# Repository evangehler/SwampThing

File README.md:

# **SwampThing**
Beginning of a standalone Juno-106 inspired DCO monosynth for UF AES. Built around Raspberry Pi Pico Microcontroller.

## **Project Status**
| Component         | Designed  | Prototyped  | PCB / Finalized |
| -----             | --------  | ----------- | --------------- |
| DCO Saw-core      | X         | X           |                 |
| DCO Pulse / PWM   | X         | X           |                 |
| DCO SUB           | X         |             |                 |
| Blend             | X         |             |                 |
| MIDI USB          | X         | X           |                 |
| MIDI DIN          | X         | X           |                 |
| VCF               | X         | X           |                 |
| EG                | X         | X           |                 |
| VCA               | X         | X           |                 |
| Power Solution    |           |             |                 |
| Output            |           |             |                 |

# Table of Contents
- [Installation / Build](#installation--build)
  - [Prereqs](#prereqs)
  - [Build Steps](#build-steps)
  - [Quick Build & Flash](#quick-build--flash)
  - [Manual Flashing](#manual-flashing)
  - [I/O Notes](#io-notes)
- [Architecture](#architecture)
  - [Component Diagram](#component-diagram)
  - [MIDI](#midi)
    - [USB MIDI](#usb-midi-implemented)
    - [DIN MIDI](#din-midi-planned)
  - [Digitally Controlled Oscillator (DCO)](#digitally-controlled-oscillator-dco)
    - [SAW](#saw)
    - [PULSE / PWM](#pulse--pwm)
    - [SUB OSC](#sub-osc)
    - [BLEND](#blend)
  - [Envelope Generator (EG)](#envelope-generator-eg)
  - [Voltage Controlled Amplifier (VCA)](#voltage-conrolled-amplifier-vca)
  - [Voltage Controlled Filter (VCF)](#voltage-controlled-filter-vcf)
  - [Power Solution](#power-solution)
- [Incomplete BOM](#incomplete-bom)

# Installation / Build
MIDI control, oscillator reset signals, charge voltage and envelope gates are derived from a Raspberry Pi Pico.

### Prereqs
- [VS Code](https://code.visualstudio.com/)
- [Raspberry Pi Pico VS Code Extension](https://marketplace.visualstudio.com/items?itemName=raspberry-pi.raspberry-pi-pico)

### Build Steps
1. Clone this repo
2. Open the `src` folder in VS Code (not the root folder!)
3. Open a PowerShell terminal in VS Code
4. Run:
```powershell
mkdir build
cd build
cmake -G "Ninja" ..
cmake --build .
```
5. The `.uf2` file will be in `build/SwampThing.uf2`

### Quick Build & Flash
- Press `Ctrl+Shift+B` to build and flash in one step - nifty!

### Manual Flashing
1. Hold BOOTSEL on your Pico and plug it in
2. Drag `SwampThing.uf2` onto the Pico drive

### I/O Notes:

| Function            | GPIO #     | 
| -----               | --------   | 
| Clock output        | 13         |
| CV output           | 14         |
| Gate output         | 12         |

# Architecture
## Component Diagram:

## MIDI:

### USB MIDI (Implemented)
SwampThing appears as a **class-compliant USB MIDI device** over the Pico’s micro-USB port using TinyUSB.

### DIN MIDI (Planned)

5-pin DIN MIDI IN (with opto-isolation and UART at 31.25 kbps) is planned. DIN and USB MIDI will eventually share the same internal note/gate handling.

## Digitally Controlled Oscillator (DCO):

### SAW
Juno-style ramp core. A TL074 op-amp integrator generates a rising ramp, NPN transistor reset discharges the timing capacitor at a rate set by the microcontroller clock. Pitch is set by the reset clock (GPIO 13). Ramp slope is set by a PWM-derived charge voltage filtered to DC (GPIO 14).

### PULSE / PWM
Saw --> Comparator, threshold = PWM

### SUB OSC
OSC --> Flip Flop, halves frequency

### BLEND
Blend control between saw and pwm

## Envelope Generator (EG):
*Currently In Development*

Design chosen

## Voltage Conrolled Amplifier (VCA):
*Currently In Development*

JFET implementation

## Voltage Controlled Filter (VCF):
*Currently In Development*

Based on Mortiz Klein / Erica Synths VCF

## Power Solution:
*Currently In Development*

 Presently planning +/- 12V, 5V rails.

 ## Prototype:

# Incomplete BOM:

| PART              | QTY       | NOTE              |
| -----             | --------  | -----------       |
| Raspberry Pi Pico | 1         | Micrcontroller    |
| TL074             | 1         | 4x Op Amp         |
| 2N3904 NPN BJT    | 1         | Reset Transistor  |

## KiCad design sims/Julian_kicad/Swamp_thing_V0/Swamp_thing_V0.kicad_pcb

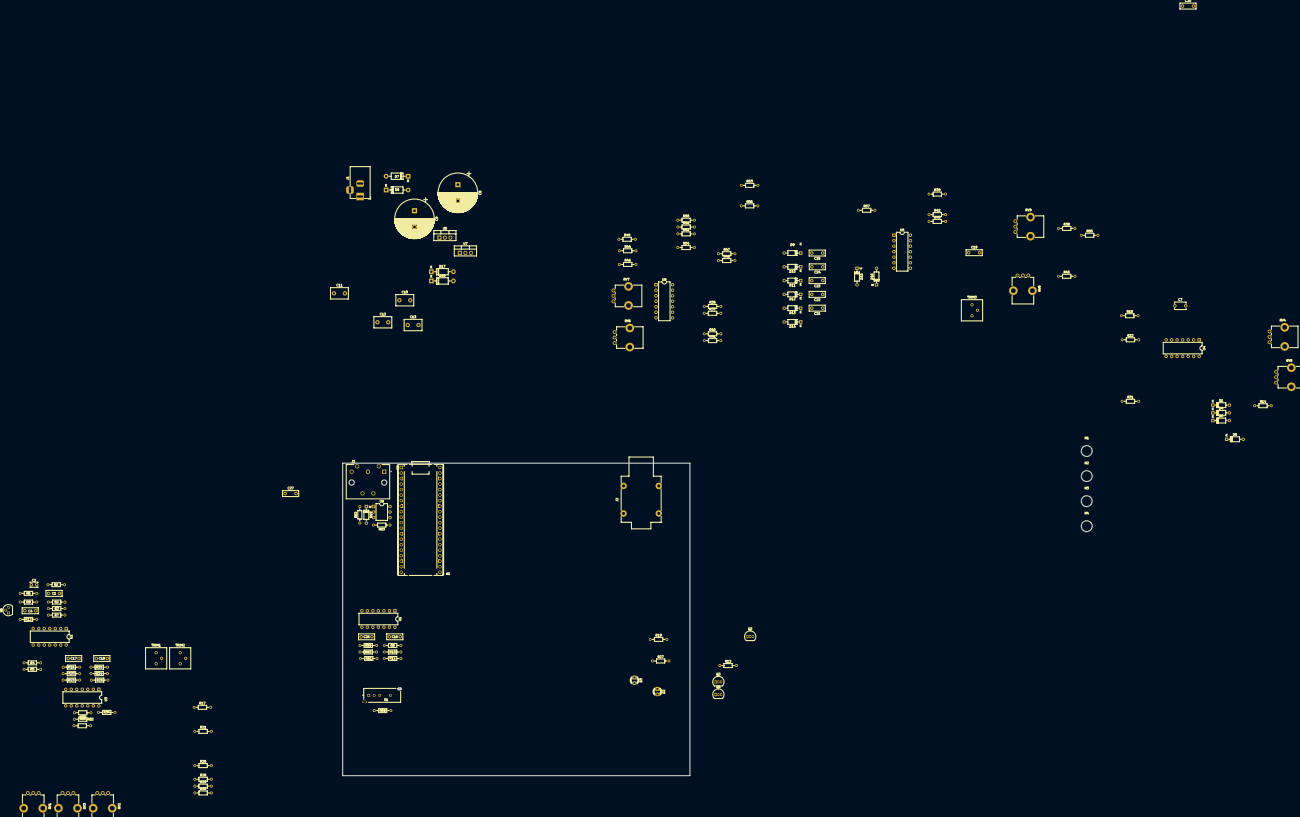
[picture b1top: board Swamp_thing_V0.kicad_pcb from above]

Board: 2 copper layers, 160.0 x 144.0 mm, 138 parts (0 on the bottom side), 107 nets, no tracks yet.

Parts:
A1: RaspberryPi_Pico; RaspberryPi_Pico_Common_THT
C1, C16, C17, C18, C19, C20, C26, C27: 100n; C_Rect_L7.2mm_W2.5mm_P5.00mm_FKS2_FKP2_MKS2_MKP2
C2: 470pF; C_Disc_D3.4mm_W2.1mm_P2.50mm
C4, C21, C22, C23, C24, C25: 1n; C_Rect_L7.2mm_W2.5mm_P5.00mm_FKS2_FKP2_MKS2_MKP2
C7: C; C_Disc_D5.1mm_W3.2mm_P5.00mm
C8, C9: 3300uF; CP_Radial_D18.0mm_P7.50mm
C10, C11, C12, C13: C; C_Disc_D8.0mm_W5.0mm_P5.00mm
D1, D4, D5, D8, D9, D10, D11, D12, D13, D14, D15, D16, D19: 1N4148; D_DO-35_SOD27_P7.62mm_Horizontal
D2, D3: LED; LED_D3.0mm
D6, D7, D17, D18: 1N4007; D_DO-41_SOD81_P10.16mm_Horizontal
H1, H2, H3, H4: MountingHole; MountingHole_5mm
J1: Barrel_Jack_MountingPin; BarrelJack_Horizontal
J2: NMJ4HFD2; Jack_6.35mm_Neutrik_NMJ4HFD2_Horizontal
J3: SDS-50J; CUI_SDS-50J
Q1: 2N3904; TO-92
Q2, Q3, Q4: 2N3904; TO-92_Inline
R1, R2, R3, R4, R5, R6, R7, R8, R9, R10, R11, R12, R13, R14, R15, R16, R17, R18, R19, R20, R21, R22, R23, R24, R25, R26, R27, R28, R29, R30, R31, R32, R33, R34, R35, R36, R37, R38, R39, R40, R41, R42, R43, R44, R45, R46, R47, R48, R49, R50, R51, R52, R53, R54, R55, R56, R57, R58, R59, R60, R61: R_US; R_Axial_DIN0204_L3.6mm_D1.6mm_P7.62mm_Horizontal
R62: 220; R_Axial_DIN0204_L3.6mm_D1.6mm_P7.62mm_Horizontal
R63: 180; R_Axial_DIN0204_L3.6mm_D1.6mm_P7.62mm_Horizontal
RV1: PWM; Potentiometer_Bourns_PTV09A-1_Single_Vertical
RV2: BLEND; Potentiometer_Bourns_PTV09A-1_Single_Vertical
RV3: SUB VOL; Potentiometer_Bourns_PTV09A-1_Single_Vertical
RV4: ATTACK; Potentiometer_Bourns_PTV09A-1_Single_Vertical
RV5: RELEASE; Potentiometer_Bourns_PTV09A-1_Single_Vertical
RV6: FILTER; Potentiometer_Bourns_PTV09A-1_Single_Vertical
RV7: FILTER EG; Potentiometer_Bourns_PTV09A-1_Single_Vertical
RV8: VOLUME; Potentiometer_Bourns_PTV09A-1_Single_Vertical
RV9: RESO; Potentiometer_Bourns_PTV09A-1_Single_Vertical
S1: SLW-178562-3A-S-D; SW_SLW-178562-3A-S-D
TRIM1, TRIM2, TRIM3: R_Potentiometer_Trim_US; Potentiometer_Bourns_3386P_Vertical
U1: 4013; DIP-14_W7.62mm
U2, U3, U4, U5, U8: TL074; DIP-14_W7.62mm
U6: L7812; TO-220-3_Vertical
U7: L7912; TO-220-3_Vertical
U9: H11L1; DIP-6_W7.62mm

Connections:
+3V3: A1.36 (3V3), R63.2, U9.6
+12V: C11.2, D17.2 (A), R4.1, R18.2, R19.2, R27.2, RV6.1, U1.14 (VDD), U2.4 (V+), U3.4 (V+), U4.4 (V+), U5.4 (V+), U6.3 (OUT), U8.4 (V+)
-12V: C13.1, D18.1 (K), R28.2, R36.1, R46.1, U2.11 (V-), U3.11 (V-), U4.11 (V-), U5.11 (V-), U7.3 (VO), U8.11 (V-)
/CLK: A1.19 (GPIO14), C2.2
/Charge PWM: A1.20 (GPIO15), R1.2
/EG_TO_LED: R13.2, U4.8, U4.9 (-)
/EG_TO_VCA: R17.2, U4.13 (-), U4.14
/EG_TO_VCF: R37.2, U4.6 (-), U4.7
/FILTER_FB: C21.1, C25.1, D15.2 (A), D16.1 (K), R57.2, U5.7
/JFET_BIAS: R21.1, R26.2
/MIDI_DIN_IN: R63.1, U9.4
/N_SUB-1: U1.2 (~Q), U1.5 (D)
/N_SUB-2: U1.9 (D), U1.12 (~Q)
/PULSE: C17.1, U2.8
/SAW: C4.2, C18.1, R12.1, U2.7, U2.9 (-)
/SUB: RV3.1, RV3.2, U2.13 (-), U2.14
/SUB-1: C26.1, U1.1 (Q), U1.11 (C)
/SUB-2: C16.1, U1.13 (Q)
/VCA_OUT: C19.1, R34.2, U3.14
/VCF_AUDIO: R47.2, R50.1, U8.1, U8.2 (-)
/VCF_BIAS: D8.1 (K), R46.2, R48.2, R49.1, R51.1
/VCF_OUT: R38.1, RV9.3, U5.1, U5.2 (-)
GND: A1.3 (GND), A1.8 (GND), A1.13 (GND), A1.18 (GND), A1.23 (GND), A1.28 (GND), A1.38 (GND), C1.2, C7.2, C8.2, C9.1, C10.1, C11.1, C12.2, C13.2, C22.1, C23.1, C24.1, C27.1, J1.2, J2.S, Q2.1 (E), Q3.1 (E), Q4.1 (E), R5.2, R6.1, R11.1, R22.2, R23.1, R25.2, R30.1, R43.1, R45.2, R49.2, R52.2, R59.2, R61.1, RV7.3, U1.4 (R), U1.6 (S), U1.7 (VSS), U1.8 (S), U1.10 (R), U2.3 (+), U2.5 (+), U3.10 (+), U3.12 (+), U5.10 (+), U6.2 (GND), U7.1 (GND), U8.5 (+), U8.10 (+), U9.5
unnamed: C1.1, R1.1, R2.2
unnamed: C2.1, R6.2, R9.2
unnamed: C16.2, R8.2
unnamed: C17.2, R16.2
unnamed: C18.2, R15.2
unnamed: C19.2, R39.2
unnamed: C20.1, RV8.2, RV8.3, U5.8
unnamed: C26.2, R58.2
unnamed: C27.2, J3.2
unnamed: D1.2 (A), R14.1
unnamed: D1.1 (K), U4.3 (+)
unnamed: D2.2 (A), R19.1
unnamed: D2.1 (K), Q3.3 (C)
unnamed: D3.2 (A), R27.1
unnamed: D3.1 (K), Q4.3 (C)
unnamed: D4.2 (A), D5.1 (K), R31.1
unnamed: D4.1 (K), RV4.3
unnamed: D5.2 (A), RV5.3
unnamed: D6.1 (K), D7.2 (A), J1.1
unnamed: D8.2 (A), R44.2, U8.7
unnamed: D9.2 (A), R53.1, R56.2
unnamed: C25.2, D9.1 (K), D10.2 (A)
unnamed: C24.2, D10.1 (K), D11.2 (A)
unnamed: C23.2, D11.1 (K), D12.2 (A), U5.3 (+)
unnamed: C22.2, D12.1 (K), D13.2 (A)
unnamed: C21.2, D13.1 (K), D14.2 (A)
unnamed: D14.1 (K), R54.2, U8.14
unnamed: D15.1 (K), D16.2 (A), R57.1, TRIM3.1, TRIM3.2, U5.6 (-)
unnamed: C8.1, C10.2, D7.1 (K), D17.1 (K), U6.1 (IN)
unnamed: C9.2, C12.1, D6.2 (A), D18.2 (A), U7.2 (VI)
unnamed: D19.2 (A), R62.1, U9.2
unnamed: D19.1 (K), J3.4, U9.1
unnamed: J2.T, R55.2
unnamed: J3.5, R62.2
unnamed: Q1.2 (B), R9.1
unnamed: Q1.3 (C), R12.2
unnamed: C4.1, Q1.1 (E), R7.1, U2.6 (-)
unnamed: Q2.2 (B), Q2.3 (C), Q3.2 (B), Q4.2 (B), R13.1
unnamed: R34.1, U3.13 (-)
unnamed: R3.1, R7.2, U2.1
unnamed: R4.2, RV1.1
unnamed: R5.1, RV1.3
unnamed: R10.1, R11.2
unnamed: R8.1, R10.2, S1.4
unnamed: R16.1, R20.2
unnamed: R17.1, TRIM1.1
unnamed: R21.2, TRIM1.2
unnamed: R24.2, R25.1
unnamed: R26.1, TRIM2.2
unnamed: R28.1, TRIM2.1
unnamed: R29.1, R30.2, TRIM1.3
unnamed: R29.2, TRIM2.3
unnamed: R31.2, U4.1
unnamed: R32.2, RV2.2
unnamed: R33.2, RV3.3
unnamed: R36.2, RV6.3
unnamed: R37.1, RV7.1
unnamed: R39.1, R42.2
unnamed: R40.1, RV6.2
unnamed: R41.1, RV7.2
unnamed: R56.1, U8.8
unnamed: R58.1, R60.2, S1.1
unnamed: R59.1, S1.2
unnamed: R60.1, R61.2
unnamed: RV9.1, TRIM3.3
unnamed: R2.1, R3.2, U2.2 (-)
unnamed: RV1.2, U2.10 (+)
unnamed: S1.3, U2.12 (+)
unnamed: R15.1, R24.1, U3.3 (+)
unnamed: RV2.1, U3.1, U3.2 (-)
unnamed: R20.1, R23.2, U3.5 (+)
unnamed: RV2.3, U3.6 (-), U3.7
unnamed: R32.1, R33.1, R35.2, U3.9 (-)
unnamed: R18.1, R22.1, U4.2 (-)
unnamed: C7.1, RV4.1, RV4.2, RV5.1, RV5.2, U4.5 (+), U4.10 (+), U4.12 (+)
unnamed: RV9.2, U5.5 (+)
unnamed: R38.2, RV8.1, U5.9 (-)
unnamed: C20.2, R45.1, U5.12 (+)
unnamed: R55.1, U5.13 (-), U5.14
unnamed: R42.1, R43.2, U8.3 (+)
unnamed: R40.2, R41.2, R44.1, U8.6 (-)
unnamed: R47.1, R48.1, R53.2, U8.9 (-)
unnamed: R51.2, R52.1, U8.12 (+)
unnamed: R50.2, R54.1, U8.13 (-)

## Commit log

2025-11-26 USB MIDI support
2025-11-26 significant pitch tracking improvement
2025-11-26 LED MIDI Flash
2025-11-26 Implemented Gate CV
2025-11-26 Update README table
2025-11-26 Remove MATLAB test
2026-01-05 Creating a directoy for my kicad project so you guys have it
2026-01-05 KiCad WIP
2026-01-06 Updated circuit / firmware so that reset pulse is sent via pico PWM rather than filtered clock
2026-02-05 Update VCF, EG, and VCA status in README
2026-03-20 Added breadboard image
